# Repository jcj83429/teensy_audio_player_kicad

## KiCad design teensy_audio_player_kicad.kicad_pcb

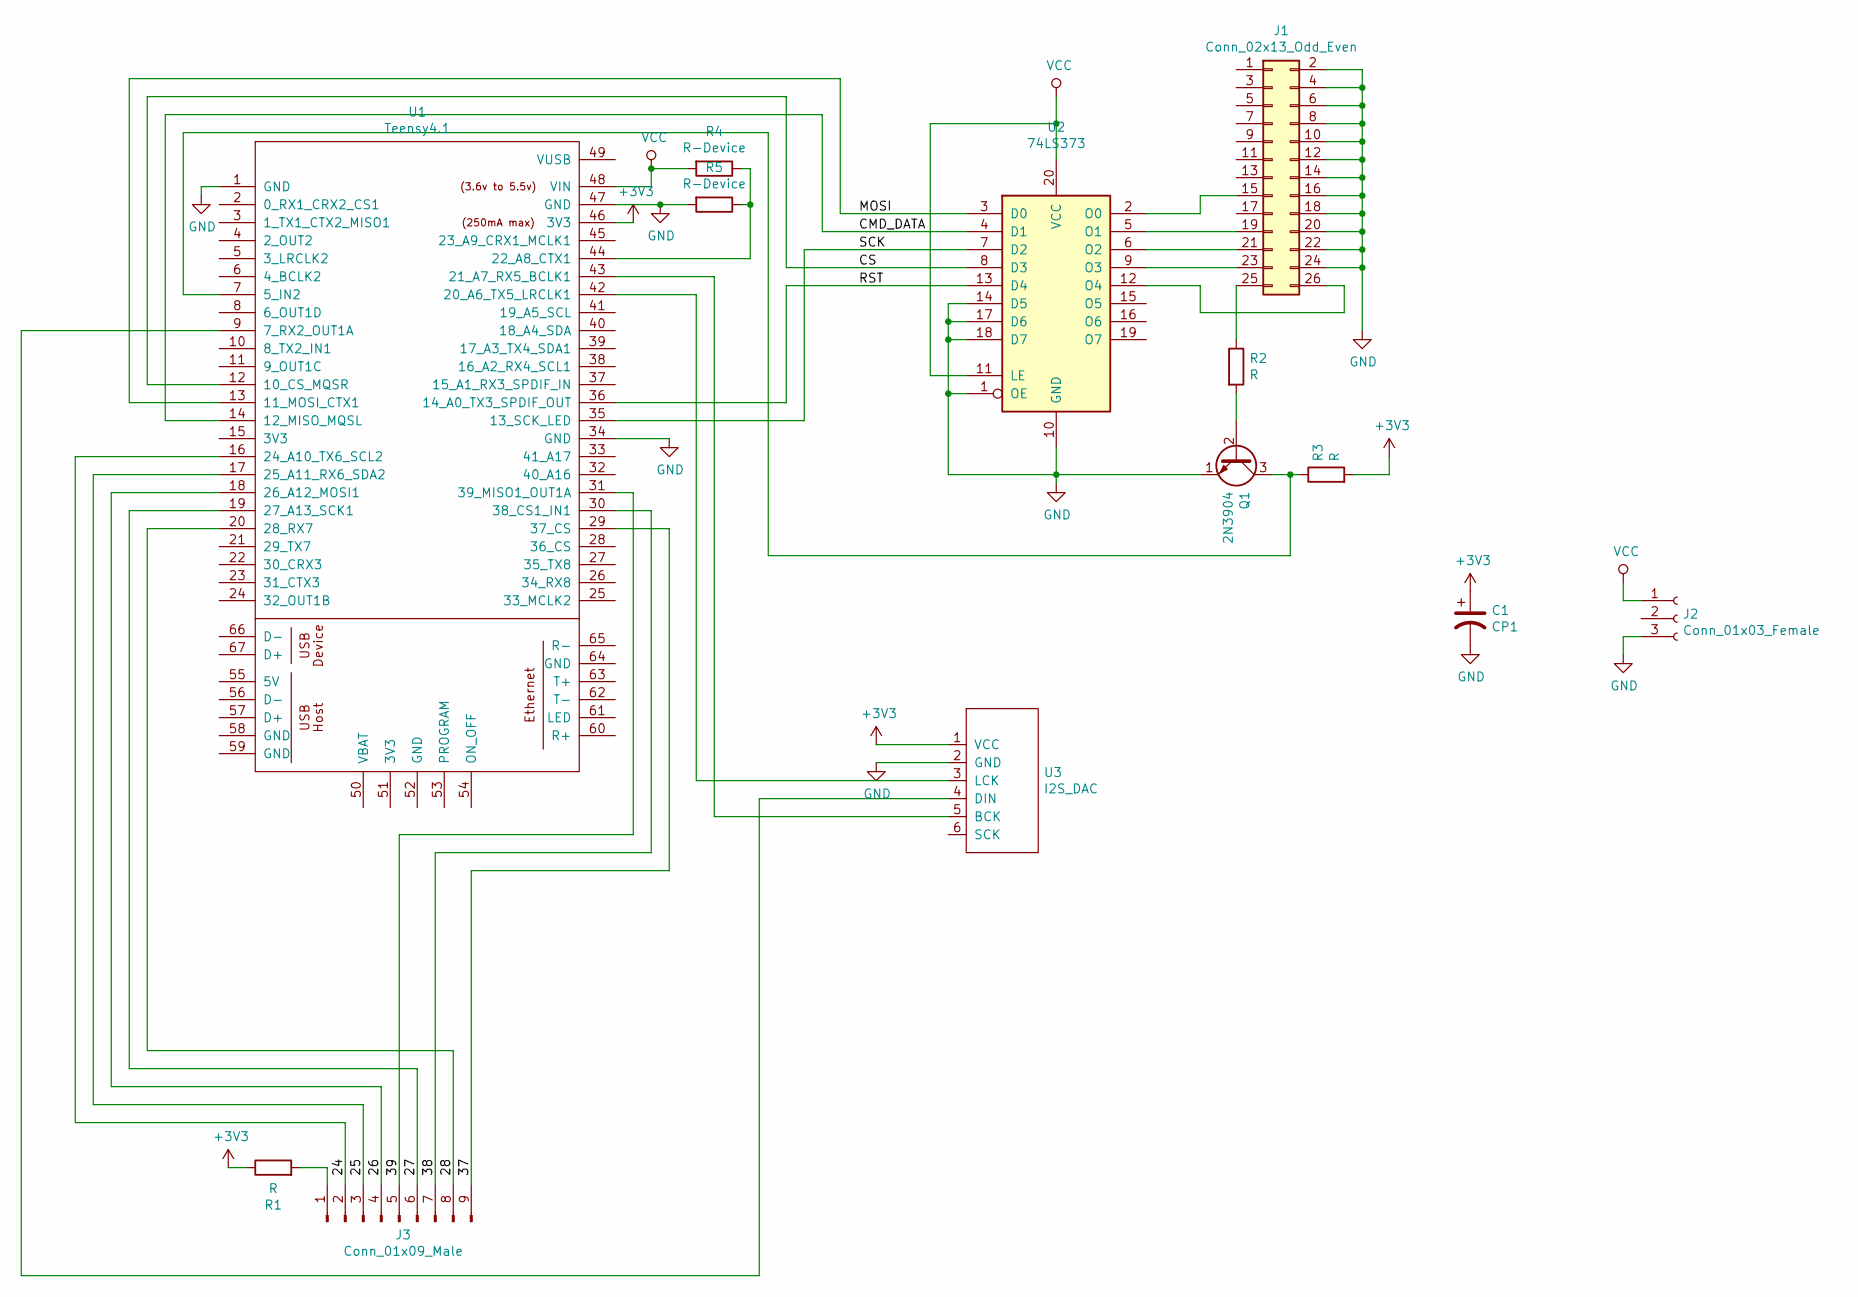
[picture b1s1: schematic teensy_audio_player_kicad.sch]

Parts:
C1: CP1; CP_Radial_D8.0mm_P3.80mm
J1: Conn_02x13_Odd_Even; IDC-Header_2x13_P2.54mm_Vertical
J2: Conn_01x03_Female; JST_XH_B3B-XH-A_1x03_P2.50mm_Vertical
J3: Conn_01x09_Male; PinHeader_1x09_P2.54mm_Vertical
Q1: 2N3904; TO-92_Inline
R1, R2: R; R_Axial_DIN0207_L6.3mm_D2.5mm_P10.16mm_Horizontal
R3: R; R_1206_3216Metric_Pad1.42x1.75mm_HandSolder
R4, R5: R-Device; R_Axial_DIN0207_L6.3mm_D2.5mm_P10.16mm_Horizontal
U1: Teensy4.1; Teensy41
U2: 74LS373; DIP-20_W7.62mm
U3: I2S_DAC; PinHeader_1x06_P2.54mm_Vertical

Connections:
+3V3: C1.1, R1.1, R3.2, U1.46 (3V3), U3.1 (VCC)
/24: J3.2, U1.16 (24_A10_TX6_SCL2)
/25: J3.3, U1.17 (25_A11_RX6_SDA2)
/26: J3.4, U1.18 (26_A12_MOSI1)
/27: J3.6, U1.19 (27_A13_SCK1)
/28: J3.8, U1.20 (28_RX7)
/37: J3.9, U1.29 (37_CS)
/38: J3.7, U1.30 (38_CS1_IN1)
/39: J3.5, U1.31 (39_MISO1_OUT1A)
/CMD_DATA: U1.14 (12_MISO_MQSL), U2.4 (D1)
/CS: U1.12 (10_CS_MQSR), U2.8 (D3)
/MOSI: U1.13 (11_MOSI_CTX1), U2.3 (D0)
/RST: U1.36 (14_A0_TX3_SPDIF_OUT), U2.13 (D4)
/SCK: U1.35 (13_SCK_LED), U2.7 (D2)
GND: C1.2, J1.2, J1.4, J1.6, J1.8, J1.10, J1.12, J1.14, J1.16, J1.18, J1.20, J1.22, J1.24, J2.3, Q1.1 (E), R5.2, U1.1 (GND), U1.34 (GND), U1.47 (GND), U2.1 (OE), U2.10 (GND), U2.14 (D5), U2.17 (D6), U2.18 (D7), U3.2 (GND)
unnamed: J1.15, U2.2 (O0)
unnamed: J1.19, U2.5 (O1)
unnamed: J1.21, U2.6 (O2)
unnamed: J1.23, U2.9 (O3)
unnamed: J1.25, R2.1
unnamed: J1.26, U2.12 (O4)
unnamed: J3.1, R1.2
unnamed: Q1.2 (B), R2.2
unnamed: Q1.3 (C), R3.1, U1.7 (5_IN2)
unnamed: R4.1, R5.1, U1.44 (22_A8_CTX1)
unnamed: U1.9 (7_RX2_OUT1A), U3.4 (DIN)
unnamed: U1.42 (20_A6_TX5_LRCLK1), U3.3 (LCK)
unnamed: U1.43 (21_A7_RX5_BCLK1), U3.5 (BCK)
VCC: J2.1, R4.2, U1.48 (VIN), U2.11 (LE), U2.20 (VCC)

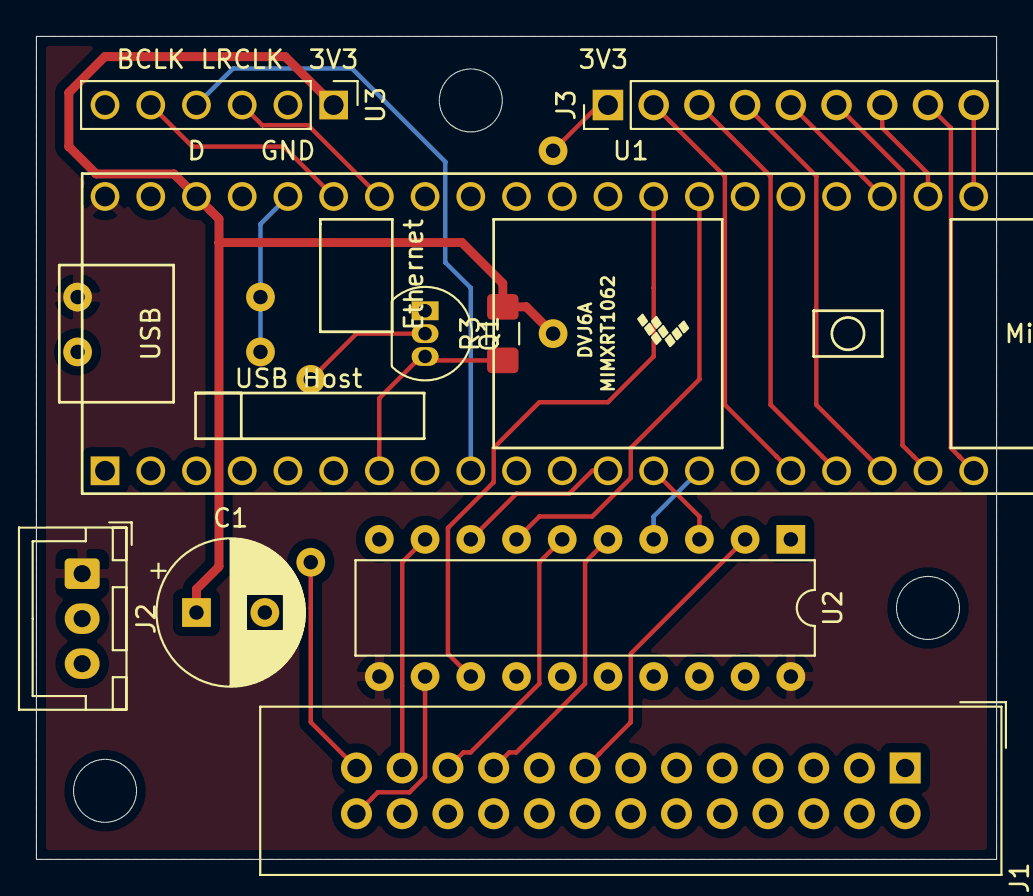
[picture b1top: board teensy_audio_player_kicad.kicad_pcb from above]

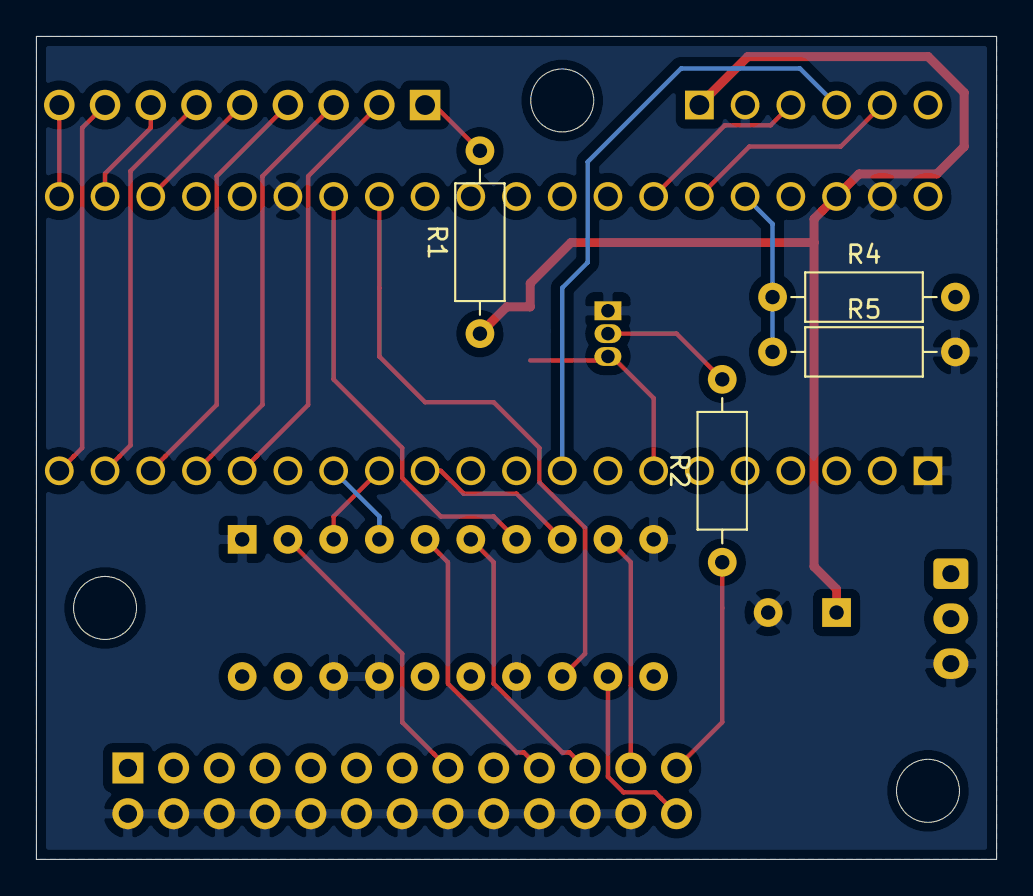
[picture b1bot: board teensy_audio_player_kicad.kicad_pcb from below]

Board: 2 copper layers, 53.3 x 45.7 mm, 13 parts (4 on the bottom side), 29 nets.

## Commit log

2020-04-11 add PCB design files
2021-04-09 update PCB for new version with teensy41
